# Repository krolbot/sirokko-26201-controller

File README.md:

# Sirokko 262.01

Контроллер для отопителя Sirokko 262.01: плата на ESP32-S3, прошивка и веб-пульт. Температура и режим работы задаются с панели с энкодером или с телефона по Wi-Fi.

[Прошивка](https://github.com/krolbot/sirokko-26201-controller/releases/latest/download/Sirokko-firmware.zip) · [Сборка и подключение](docs/assembly.md) · [Руководство пользователя](docs/user-guide.md) · [Компоненты и цены](hardware/BOM.md)

## Возможности

- Поддерживает температуру помещения или работает на заданном вручную уровне.
- Управляет розжигом и охлаждением, следит за температурой выхлопа и нагретого воздуха.
- Показывает графики температур, записывает измерения в CSV и отключает нагрев по таймеру.
- Обновляется по Wi-Fi.

## Устройство

Двухслойная плата **95 × 75 мм** питается от стабилизированного блока **12 или 24 В**. На ней устанавливаются **YD-ESP32-S3 N16R8 V1.4** и два модуля **MAX31856** для термопар K. Температуру помещения измеряет **DS18B20**.

Свеча и топливная муфта подключаются через внешние реле с катушками под напряжение выбранного БП. Двигателем управляет **HC-160A S2**. Силовая проводка отопителя проходит отдельно от платы контроллера.

Плата и прошивка пока не испытывались на собранном отопителе.

## Файлы проекта

| Каталог | Содержимое |
|---|---|
| [hardware](hardware/README.md) | Схема и плата Fusion Electronics, PDF, библиотека и ведомость компонентов |
| [firmware](firmware/README.md) | Исходники и сборка прошивки ESP32-S3 и веб-интерфейса Svelte |
| [manufacturing](manufacturing/README.md) | Gerber, параметры заказа платы, сборочный чертёж и монтажные координаты |
| [docs](docs/) | Сборка, подключение и использование |

[Выпуски](https://github.com/krolbot/sirokko-26201-controller/releases) · [Вопросы и ошибки](https://github.com/krolbot/sirokko-26201-controller/issues)

## Лицензии

Общая лицензия проекта не назначена. Лицензии сторонних материалов: [библиотеки KiCad](hardware/KICAD_LIBRARIES_LICENSE.md), [прошивка](firmware/README.md#сторонние-материалы), [веб-интерфейс](firmware/web_ui/THIRD_PARTY_NOTICES.txt).

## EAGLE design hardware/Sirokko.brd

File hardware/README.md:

# Плата контроллера

Двухслойная плата 95 × 75 мм с питанием от стабилизированного БП 12 или 24 В. ESP32 и модули термопар устанавливаются в колодки; силовые нагрузки подключаются через внешние реле и моторный контроллер.

## Модули

- YD-ESP32-S3 N16R8 V1.4 с внешней антенной, два ряда по 22 контакта.
- Два модуля MAX31856 с геометрией и распиновкой Adafruit 3263.
- Панель ST7789 2,4″ с энкодером EC11 и кнопкой KEY0, питание и логика 3,3 В.
- Моторный контроллер HC-160A S2 и две катушки реле под напряжение БП, до 0,25 А каждая.

## Питание и защита

F1 на 2 А и двунаправленный TVS SMBJ30CA защищают вход перед TPS26600. TPS26600 отключает питание при переполюсовке, перенапряжении, перегрузке и коротком замыкании. При перегрузке он повторяет попытки запуска; также предусмотрена тепловая защита.

| Параметр | Значение |
|---|---|
| Рабочее питание | Стабилизированный БП 12 или 24 В DC |
| Запуск после подачи питания | Около 10,2 В; расчётный диапазон 9,72–10,81 В |
| Отключение при снижении питания | Около 9,4 В; расчётный диапазон 8,93–9,93 В |
| Отключение по перенапряжению | Около 28 В; расчётный диапазон 26,59–29,77 В |
| Возврат после перенапряжения | Около 25,9 В; расчётный диапазон 24,65–27,34 В |
| Ограничение входного тока | Около 1 А |
| Плавный пуск | Около 10 мс при 12 В и 21 мс при 24 В |
| Выход K7805-1000R3 | 5 В / 1 А; бюджет электроники — 0,70 А |
| Питание датчиков и панели | 3,3 В от TLV1117LV33 |

Плата работает от 12 и 24 В без переключения. Катушки реле выбираются под напряжение БП: защита с порогом 28 В не защищает катушки 12 В от подключения к 24 В.

Пороги TPS26600 задают R101 (249 кОм), R103 (21 кОм) и R102 (12 кОм). Расчётные диапазоны учитывают допуск резисторов 1%, ТКС ±100 ppm/°C при −40…+85 °C, допуски порогов и входных токов из [даташита TI](https://www.ti.com/lit/ds/symlink/tps2660.pdf).

На входе K7805 установлен C101, 10 мкФ, 50 В, X7R — по типовой схеме [Mornsun](https://www.mornsun-power.com/public/uploads/pdf/K78xx-1000R3(L).pdf) для питания 12/24 В. Порог отключения TPS26600 с учётом допусков ниже 30 В.

Периферия питается от отдельного стабилизатора 3,3 В. Тепло от его площадки U102.4 отводится в сплошной полигон +3,3 В на верхнем слое. Ключи AO3422 управляют катушками реле; D20/D21 подавляют выбросы напряжения, RP20/RP21 удерживают ключи выключенными при старте ESP32. Внешние сигнальные линии защищены сборками SRV05-4.

## Файлы

| Файл | Назначение |
|---|---|
| [Sirokko.sch](Sirokko.sch), [Sirokko.brd](Sirokko.brd) | Связанные схема и плата Fusion Electronics в формате EAGLE |
| [Sirokko.lbr](Sirokko.lbr), [Sirokko-parts.lbr](Sirokko-parts.lbr) | Библиотеки компонентов и посадочных мест |
| [Sirokko.edru](Sirokko.edru) | Правила проектирования и проверки платы в Fusion |
| [schematic.pdf](schematic.pdf) | Схема в PDF |
| [BOM.md](BOM.md), [bom.csv](bom.csv) | Ведомость компонентов с артикулами и ценами |

Схему и плату открывают вместе в Fusion Electronics. Символы и посадочные места встроены в файлы. После импорта платы загрузите `Sirokko.edru` через **Design Rules → Load**: формат EAGLE не сохраняет все правила Fusion.

[Крепление и подключения](../docs/assembly.md) · [Изготовление платы](../manufacturing/README.md) · [Лицензии библиотек](KICAD_LIBRARIES_LICENSE.md)

## Верхний слой

## Нижний слой (вид сверху)

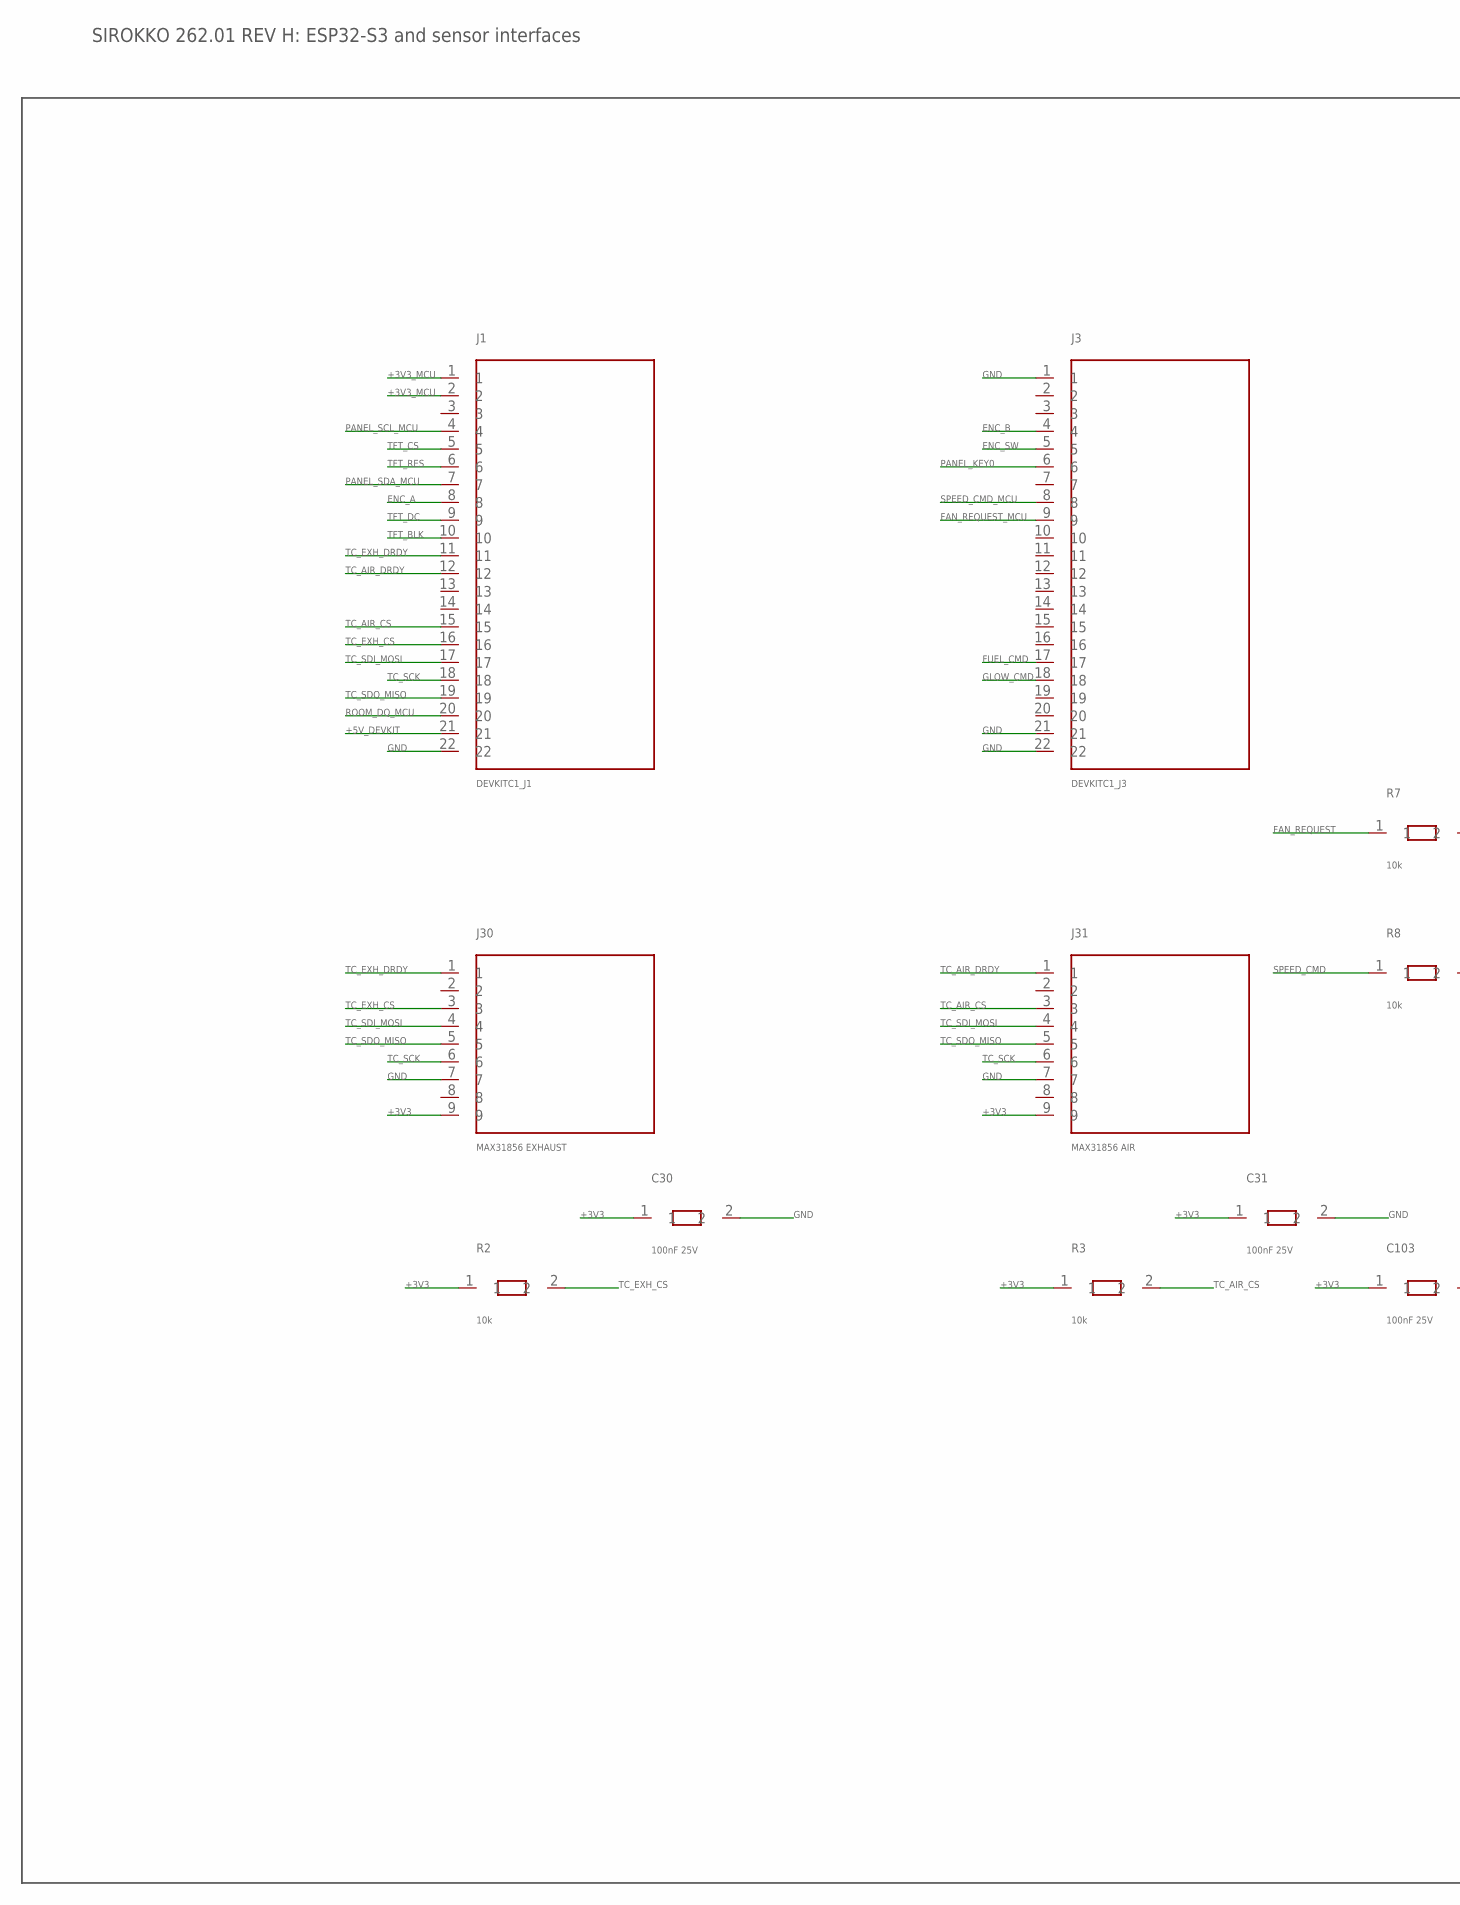
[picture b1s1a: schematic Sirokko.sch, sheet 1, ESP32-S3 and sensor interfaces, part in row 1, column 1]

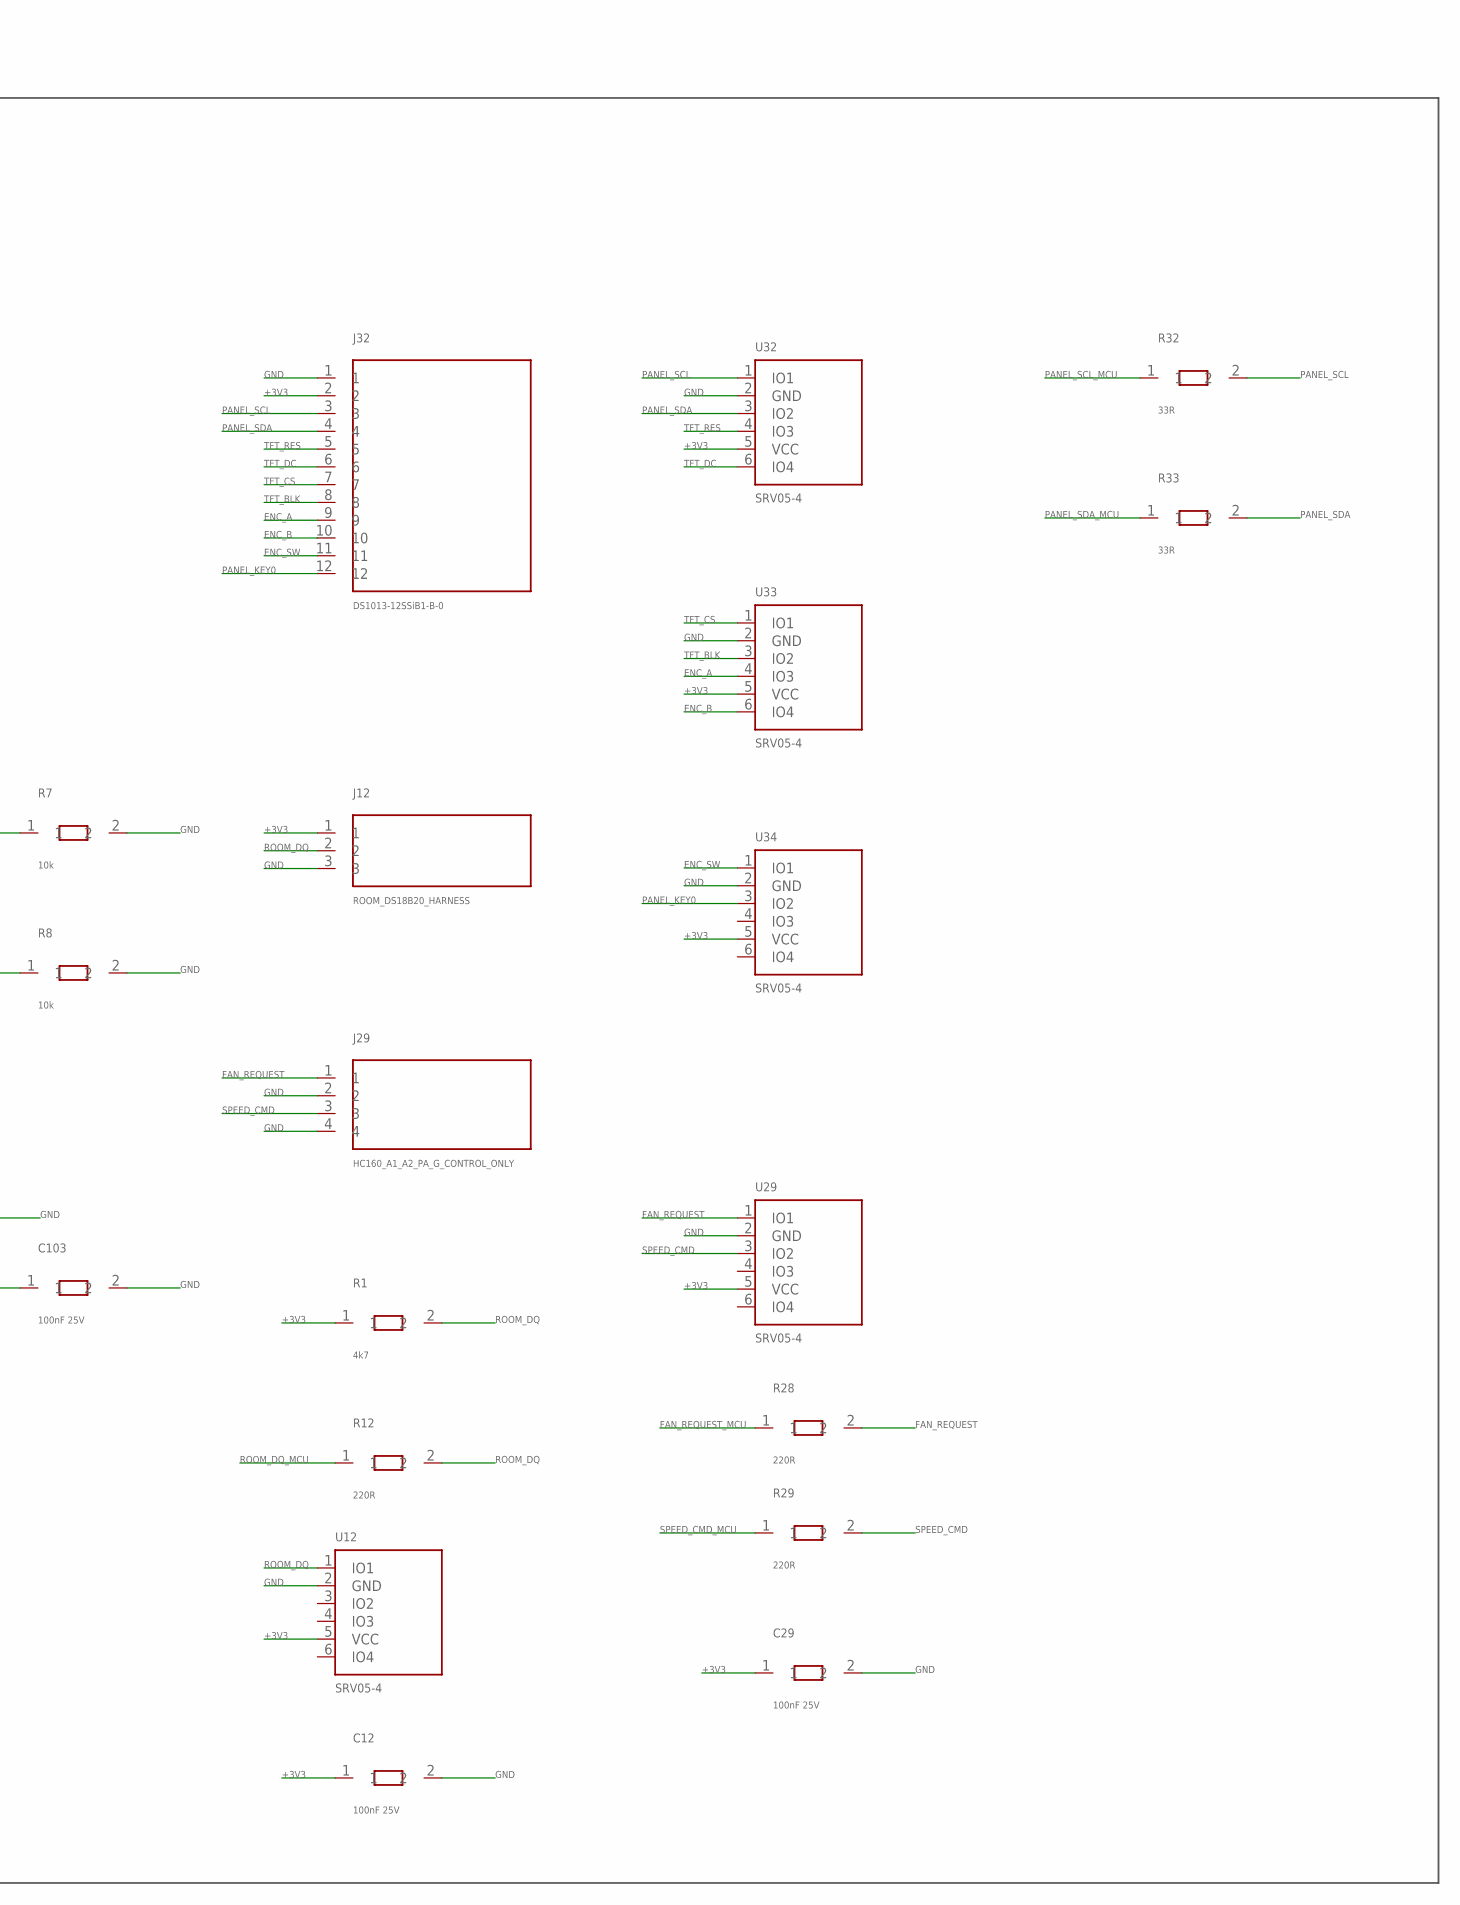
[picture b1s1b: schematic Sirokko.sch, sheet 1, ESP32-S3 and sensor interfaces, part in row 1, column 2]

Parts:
C12, C29, C30, C31, C103: 100nF 25V; C0805; MPN CC0805KRX7R8BB104
J1: DEVKITC1_J1; SOCKET_1X22_P2.54; MPN DS1023-1x40
J3: DEVKITC1_J3; SOCKET_1X22_P2.54; MPN DS1023-1x40
J12: ROOM_DS18B20_HARNESS; TERM_5.08_3; MPN DG127-5.08-03P-14-1000Z(H)
J29: HC160_A1_A2_PA_G_CONTROL_ONLY; TERM_5.08_4; MPN DG127-5.08-02P-14-00A(H)
J30: MAX31856 EXHAUST; SOCKET_MAX31856; MPN DS1023-1x40
J31: MAX31856 AIR; SOCKET_MAX31856; MPN DS1023-1x40
J32: DS1013-12SSiB1-B-0; DS1013_12SSIB1; MPN DS1013-12SSiB1-B-0
R1: 4k7; R0805; MPN RC0805FR-074K7L
R2, R3, R7, R8: 10k; R0805; MPN RC0805FR-0710KL
R12, R28, R29: 220R; R0805; MPN RC0805FR-07220RL
R32, R33: 33R; R0805; MPN RC0805FR-0733RL
U12, U29, U32, U33, U34: SRV05-4; SRV05_SOT23_6

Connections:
+3V3: C12.1, C29.1, C30.1, C31.1, C103.1, J12.1, J30.9, J31.9, J32.2, R1.1, R2.1, R3.1, U12.5 (VCC), U29.5 (VCC), U32.5 (VCC), U33.5 (VCC), U34.5 (VCC); also elsewhere on the board
+3V3_MCU: J1.1, J1.2
+5V_DEVKIT: J1.21; also elsewhere on the board
ENC_A: J1.8, J32.9, U33.4 (IO3)
ENC_B: J3.4, J32.10, U33.6 (IO4)
ENC_SW: J3.5, J32.11, U34.1 (IO1)
FAN_REQUEST: J29.1, R7.1, R28.2, U29.1 (IO1)
FAN_REQUEST_MCU: J3.9, R28.1
FUEL_CMD: J3.17; also elsewhere on the board
GLOW_CMD: J3.18; also elsewhere on the board
GND: C12.2, C29.2, C30.2, C31.2, C103.2, J1.22, J3.1, J3.21, J3.22, J12.3, J29.2, J29.4, J30.7, J31.7, J32.1, R7.2, R8.2, U12.2 (GND), U29.2 (GND), U32.2 (GND), U33.2 (GND), U34.2 (GND); also elsewhere on the board
PANEL_KEY0: J3.6, J32.12, U34.3 (IO2)
PANEL_SCL: J32.3, R32.2, U32.1 (IO1)
PANEL_SCL_MCU: J1.4, R32.1
PANEL_SDA: J32.4, R33.2, U32.3 (IO2)
PANEL_SDA_MCU: J1.7, R33.1
ROOM_DQ: J12.2, R1.2, R12.2, U12.1 (IO1)
ROOM_DQ_MCU: J1.20, R12.1
SPEED_CMD: J29.3, R8.1, R29.2, U29.3 (IO2)
SPEED_CMD_MCU: J3.8, R29.1
TC_AIR_CS: J1.15, J31.3, R3.2
TC_AIR_DRDY: J1.12, J31.1
TC_EXH_CS: J1.16, J30.3, R2.2
TC_EXH_DRDY: J1.11, J30.1
TC_SCK: J1.18, J30.6, J31.6
TC_SDI_MOSI: J1.17, J30.4, J31.4
TC_SDO_MISO: J1.19, J30.5, J31.5
TFT_BLK: J1.10, J32.8, U33.3 (IO2)
TFT_CS: J1.5, J32.7, U33.1 (IO1)
TFT_DC: J1.9, J32.6, U32.6 (IO4)
TFT_RES: J1.6, J32.5, U32.4 (IO3)

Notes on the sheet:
SIROKKO 262.01 REV H: ESP32-S3 and sensor interfaces

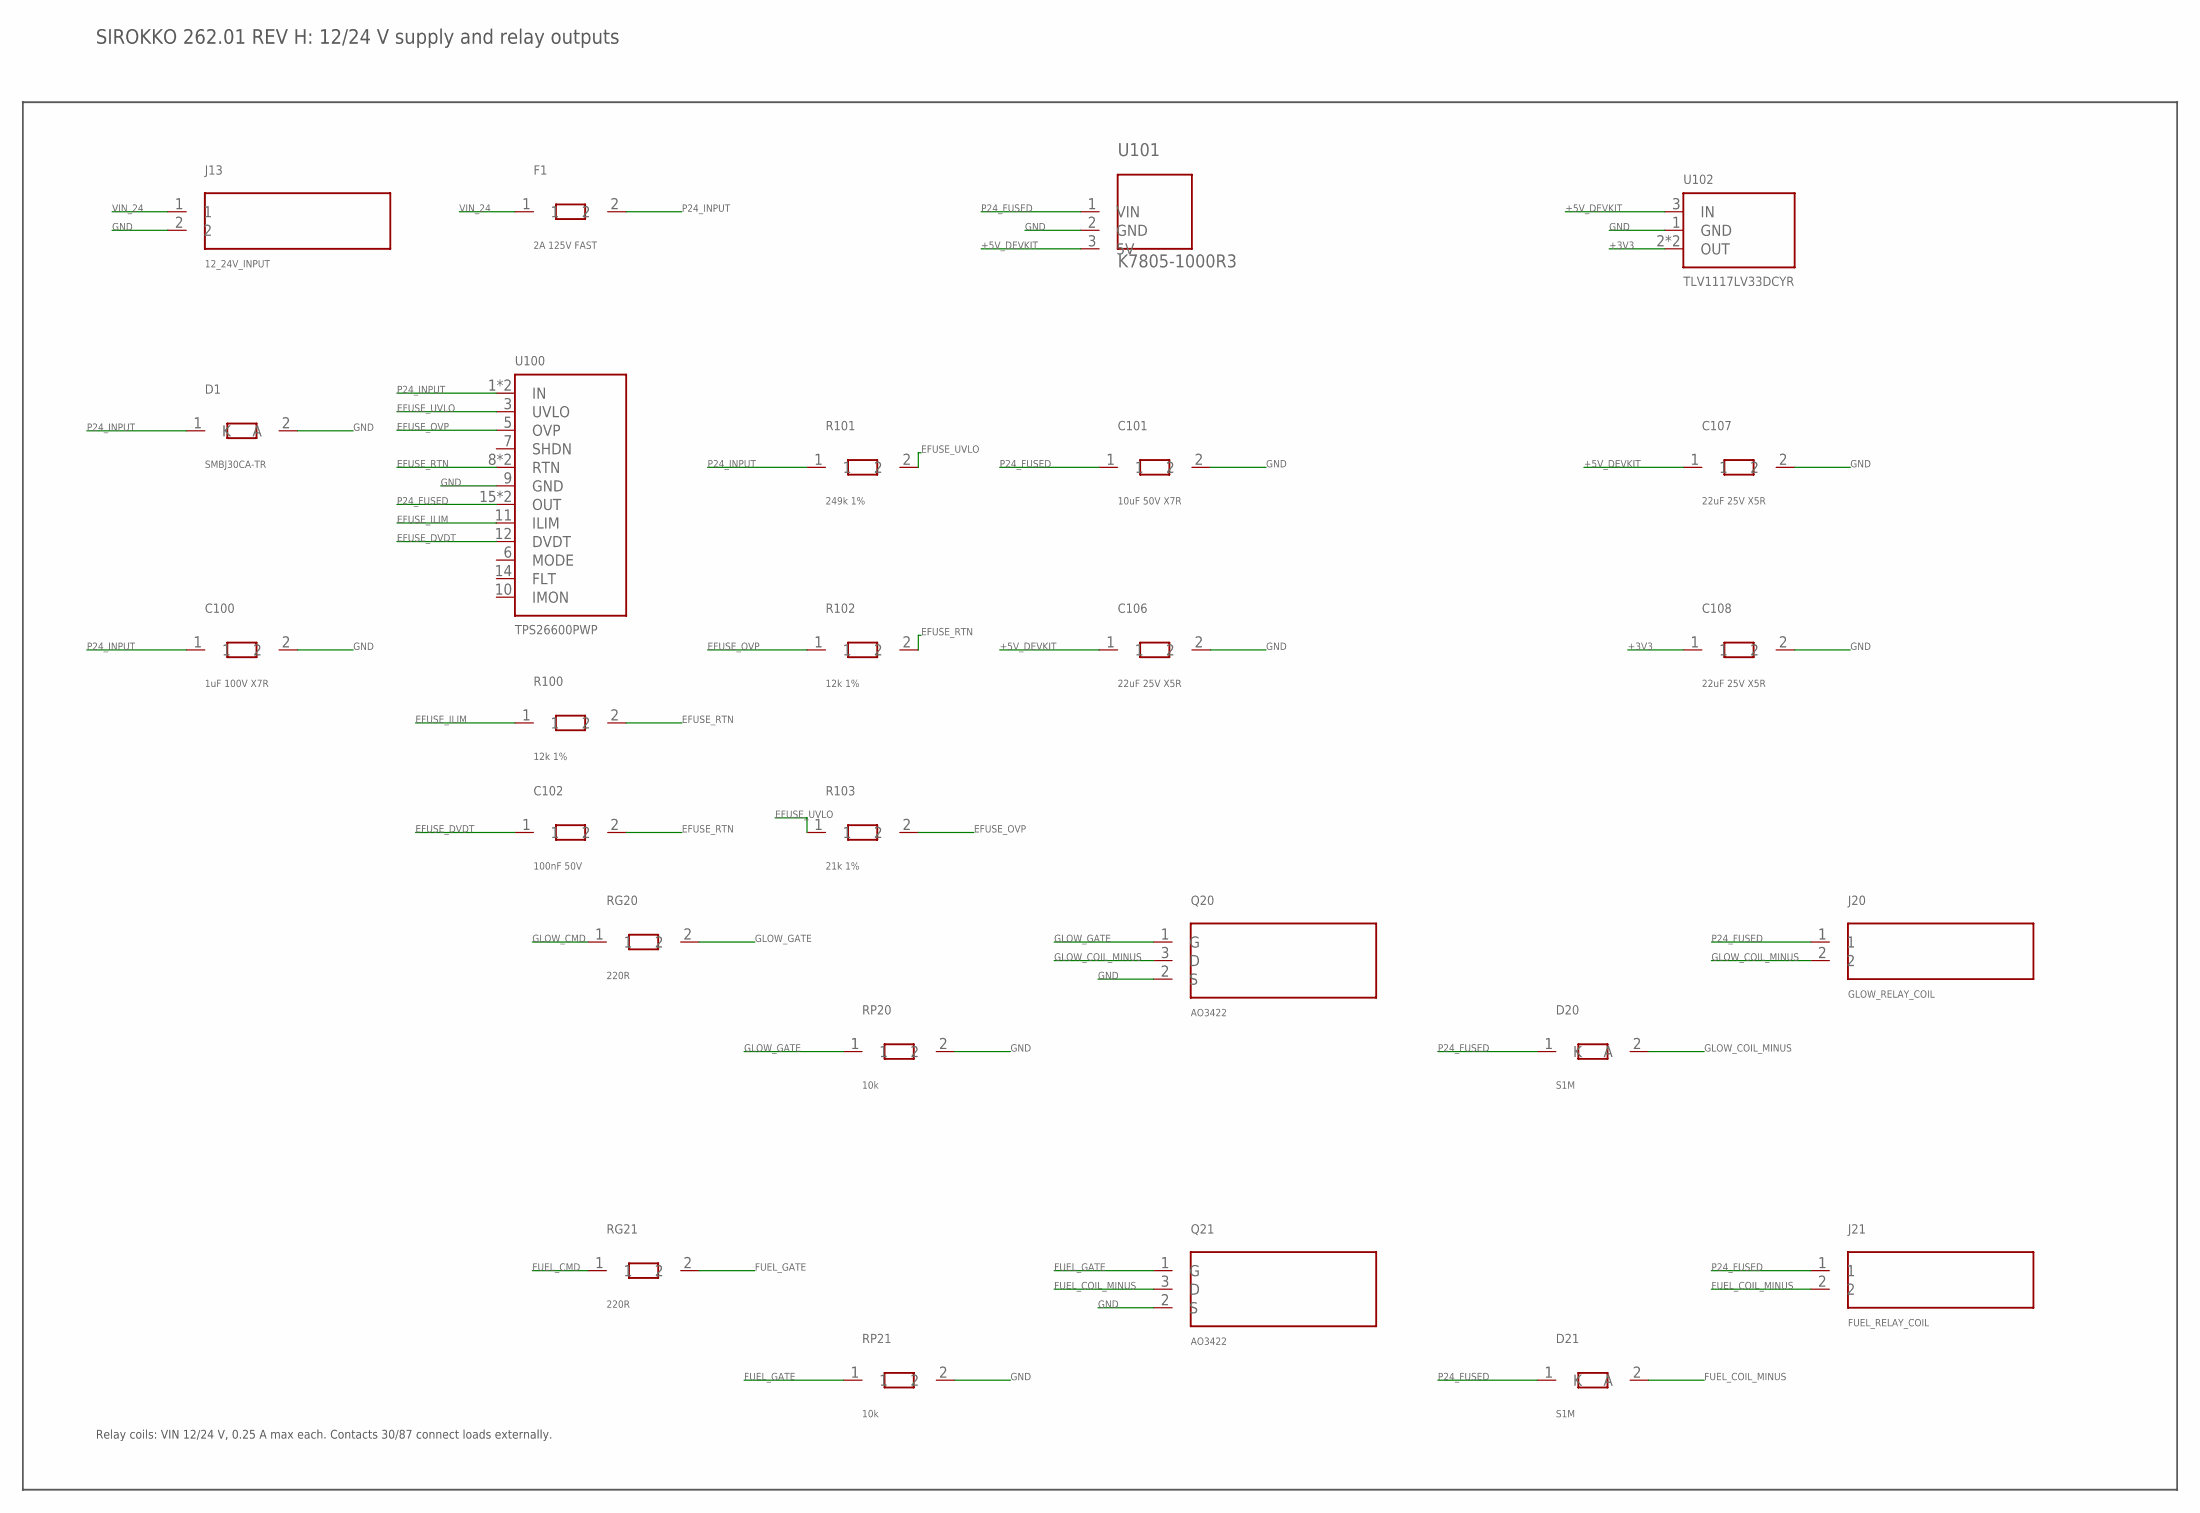
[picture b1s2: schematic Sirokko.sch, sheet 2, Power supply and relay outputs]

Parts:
C100: 1uF 100V X7R; C1206; MPN CC1206KKX7R0BB105
C101: 10uF 50V X7R; C1210; MPN GRM32ER71H106KA12L
C102: 100nF 50V; C1206; MPN CL31B104KBCNNNC
C106, C107, C108: 22uF 25V X5R; C1206; MPN CL31A226KAHNNNE
D1: SMBJ30CA-TR; SMB; MPN SMBJ30CA-TR
D20, D21: S1M; SMA; MPN S1M-13-F
F1: 2A 125V FAST; FUSE2410; MPN 0451002.MRL
J13: 12_24V_INPUT; TERM_5.08_2; MPN DG127-5.08-02P-14-00A(H)
J20: GLOW_RELAY_COIL; TERM_5.08_2; MPN DG127-5.08-02P-14-00A(H)
J21: FUEL_RELAY_COIL; TERM_5.08_2; MPN DG127-5.08-02P-14-00A(H)
Q20, Q21: AO3422; AO3422_SOT23
R100, R102: 12k 1%; R0805; MPN RC0805FR-0712KL
R101: 249k 1%; R0805; MPN RC0805FR-07249KL
R103: 21k 1%; R0805; MPN RC0805FR-0721KL
RG20, RG21: 220R; R0805; MPN RC0805FR-07220RL
RP20, RP21: 10k; R0805; MPN RC0805FR-0710KL
U100: TPS26600PWP; TPS26600_PWP
U101: K7805-1000R3; K7805_1000R3; MPN K7805-1000R3
U102: TLV1117LV33DCYR; TLV1117LV_DCY

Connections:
+3V3: C108.1, U102.2 (OUT), U102.4 (OUT); also elsewhere on the board
+5V_DEVKIT: C106.1, C107.1, U101.3 (5V), U102.3 (IN); also elsewhere on the board
EFUSE_DVDT: C102.1, U100.12 (DVDT)
EFUSE_ILIM: R100.1, U100.11 (ILIM)
EFUSE_OVP: R102.1, R103.2, U100.5 (OVP)
EFUSE_RTN: C102.2, R100.2, R102.2, U100.8 (RTN), U100.17 (RTN)
EFUSE_UVLO: R101.2, R103.1, U100.3 (UVLO)
FUEL_CMD: RG21.1; also elsewhere on the board
FUEL_COIL_MINUS: D21.2 (A), J21.2, Q21.3 (D)
FUEL_GATE: Q21.1 (G), RG21.2, RP21.1
GLOW_CMD: RG20.1; also elsewhere on the board
GLOW_COIL_MINUS: D20.2 (A), J20.2, Q20.3 (D)
GLOW_GATE: Q20.1 (G), RG20.2, RP20.1
GND: C100.2, C101.2, C106.2, C107.2, C108.2, D1.2 (A), J13.2, Q20.2 (S), Q21.2 (S), RP20.2, RP21.2, U100.9 (GND), U101.2 (GND), U102.1 (GND); also elsewhere on the board
P24_FUSED: C101.1, D20.1 (K), D21.1 (K), J20.1, J21.1, U100.15 (OUT), U100.16 (OUT), U101.1 (VIN)
P24_INPUT: C100.1, D1.1 (K), F1.2, R101.1, U100.1 (IN), U100.2 (IN)
VIN_24: F1.1, J13.1

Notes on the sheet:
SIROKKO 262.01 REV H: 12/24 V supply and relay outputs
Relay coils: VIN 12/24 V, 0.25 A max each. Contacts 30/87 connect loads externally.

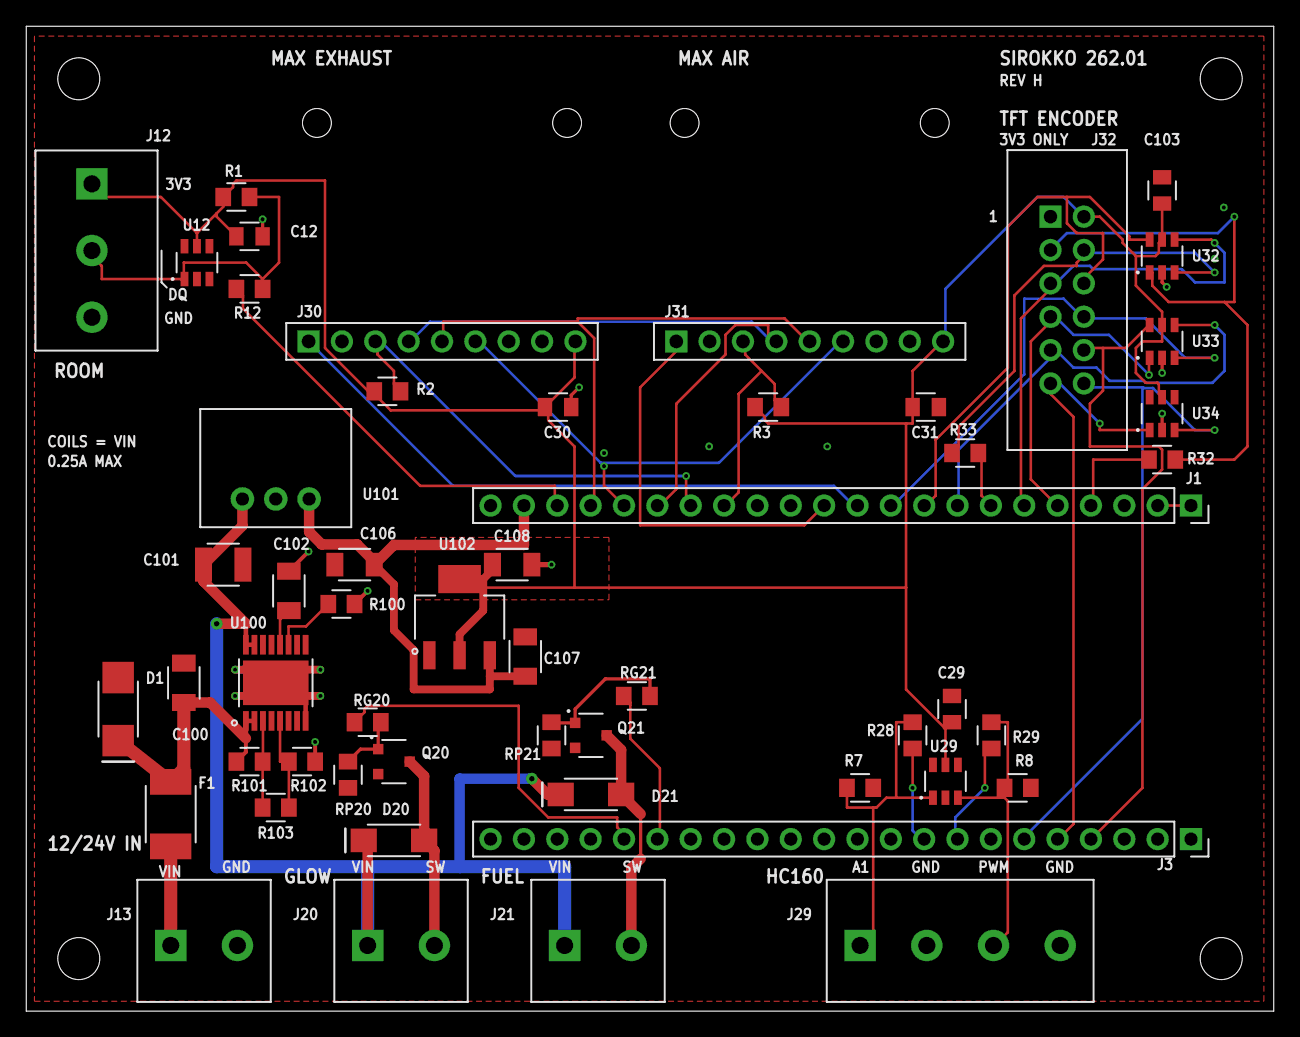
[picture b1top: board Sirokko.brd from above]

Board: 2 copper layers, 95.0 x 75.0 mm, 53 parts (0 on the bottom side), 43 nets.

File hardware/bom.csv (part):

Reference,Value,MPN,Package,Quantity,Mount,Side,Note,Supplier,SupplierURL,UnitPriceRUB,PriceUnit,PriceDate,MinimumOrder,OrderMultiple,PriceOffer
C12,100nF 25V,CC0805KRX7R8BB104,C0805,1,SMT,top,X7R; питание защиты сигналов,ЧипДип,https://www.chipdip.ru/product/0.1mkf-x7r-25v-10-0805-cc0805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,5,piece,2026-11-16,5,5,Основное предложение
C29,100nF 25V,CC0805KRX7R8BB104,C0805,1,SMT,top,X7R; питание защиты сигналов,ЧипДип,https://www.chipdip.ru/product/0.1mkf-x7r-25v-10-0805-cc0805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,5,piece,2026-11-16,5,5,Основное предложение
C30,100nF 25V,CC0805KRX7R8BB104,C0805,1,SMT,top,X7R; питание MAX31856,ЧипДип,https://www.chipdip.ru/product/0.1mkf-x7r-25v-10-0805-cc0805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,5,piece,2026-11-16,5,5,Основное предложение
C31,100nF 25V,CC0805KRX7R8BB104,C0805,1,SMT,top,X7R; питание MAX31856,ЧипДип,https://www.chipdip.ru/product/0.1mkf-x7r-25v-10-0805-cc0805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,5,piece,2026-11-16,5,5,Основное предложение
C100,1uF 100V X7R,CC1206KKX7R0BB105,C1206,1,SMT,top,X7R; вход U100,ЧипДип,https://www.chipdip.ru/product/1mkf-x7r-100v-10-1206-cc1206k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,9,piece,2026-11-16,5,5,Основное предложение
C101,10uF 50V X7R,GRM32ER71H106KA12L,C1210,1,SMT,top,X7R; вход U101 после электронной защиты,ЧипДип,https://www.chipdip.ru/product/10mkf-x7r-50v-10-1210-grm32er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,28,piece,2026-11-16,5,5,Основное предложение
C102,100nF 50V,CL31B104KBCNNNC,C1206,1,SMT,top,X7R; плавный пуск U100,ЧипДип,https://www.chipdip.ru/product/0.1mkf-x7r-50v-10-1206-cl31b1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,6,piece,2026-11-16,1,1,Основное предложение
C103,100nF 25V,CC0805KRX7R8BB104,C0805,1,SMT,top,X7R; питание защиты панели,ЧипДип,https://www.chipdip.ru/product/0.1mkf-x7r-25v-10-0805-cc0805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,5,piece,2026-11-16,5,5,Основное предложение
C106,22uF 25V X5R,CL31A226KAHNNNE,C1206,1,SMT,top,"X5R, 25 В",ЧипДип,https://www.chipdip.ru/product/22mkf-x5r-25v-10-1206-cl31a22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,12,piece,2026-11-16,1,1,Основное предложение
C107,22uF 25V X5R,CL31A226KAHNNNE,C1206,1,SMT,top,X5R; вход U102,ЧипДип,https://www.chipdip.ru/product/22mkf-x5r-25v-10-1206-cl31a22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,12,piece,2026-11-16,1,1,Основное предложение
C108,22uF 25V X5R,CL31A226KAHNNNE,C1206,1,SMT,top,X5R; выход U102,ЧипДип,https://www.chipdip.ru/product/22mkf-x5r-25v-10-1206-cl31a22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,12,piece,2026-11-16,1,1,Основное предложение
D1,SMBJ30CA-TR,SMBJ30CA-TR,SMB,1,SMT,top,Двунаправленный TVS; полярности нет,ЧипДип,https://www.chipdip.ru/product/smbj30ca-tr-diod-zaschitnyy-6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,19,piece,2026-11-16,1,1,Основное предложение
D20,S1M,S1M-13-F,SMA,1,SMT,top,Катод — к плюсу катушки,ЧипДип,https://www.chipdip.ru/product/s1m-13-f-diod-vypryamitelnyy-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,5,piece,2026-11-16,1,1,Основное предложение
D21,S1M,S1M-13-F,SMA,1,SMT,top,Катод — к плюсу катушки,ЧипДип,https://www.chipdip.ru/product/s1m-13-f-diod-vypryamitelnyy-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,5,piece,2026-11-16,1,1,Основное предложение
F1,2A 125V FAST,0451002.MRL,FUSE2410,1,SMT,top,,ЧипДип,https://www.chipdip.ru/product/0451002-mrl-2a-125v-2410-pred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,23,piece,2026-11-16,1,1,Основное предложение
J1,DEVKITC1_J1,DS1023-1x40,SOCKET_1X22_P2.54,1,THT,top,Отрезок 22 контакта; две планки по 40 контактов на J1/J3/J30/J31,ЧипДип,https://www.chipdip.ru/product/pbs-40-ds1023-1x40-gnezdo-na-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,28,40-pin strip,2026-11-16,1,1,Основное предложение
J3,DEVKITC1_J3,DS1023-1x40,SOCKET_1X22_P2.54,1,THT,top,Отрезок 22 контакта; две планки по 40 контактов на J1/J3/J30/J31,ЧипДип,https://www.chipdip.ru/product/pbs-40-ds1023-1x40-gnezdo-na-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,28,40-pin strip,2026-11-16,1,1,Основное предложение
J12,ROOM_DS18B20_HARNESS,DG127-5.08-03P-14-1000Z(H),TERM_5.08_3,1,THT,top,,ЧипДип,https://www.chipdip.ru/product/dg127-5.08-03p-14-1000z-h-kle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,45,piece,2026-11-16,1,1,Альтернативное предложение
J13,12_24V_INPUT,DG127-5.08-02P-14-00A(H),TERM_5.08_2,1,THT,top,1: VIN 12/24 В; 2: GND,ЧипДип,https://www.chipdip.ru/product/dg127-5.08-02p-14-00a-h-klemm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,28,piece,2026-11-16,10,10,Основное; альтернатива для 5 плат: 19 ₽ от 32 шт.
J20,GLOW_RELAY_COIL,DG127-5.08-02P-14-00A(H),TERM_5.08_2,1,THT,top,"Катушка реле до 0,25 А; 1: VIN 12/24 В; 2: коммутируемый минус",ЧипДип,https://www.chipdip.ru/product/dg127-5.08-02p-14-00a-h-klemm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,28,piece,2026-11-16,10,10,Основное; альтернатива для 5 плат: 19 ₽ от 32 шт.
J21,FUEL_RELAY_COIL,DG127-5.08-02P-14-00A(H),TERM_5.08_2,1,THT,top,"Катушка реле до 0,25 А; 1: VIN 12/24 В; 2: коммутируемый минус",ЧипДип,https://www.chipdip.ru/product/dg127-5.08-02p-14-00a-h-klemm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,28,piece,2026-11-16,10,10,Основное; альтернатива для 5 плат: 19 ₽ от 32 шт.
J29,HC160_A1_A2_PA_G_CONTROL_ONLY,DG127-5.08-02P-14-00A(H),TERM_5.08_4,1,THT,top,Два состыкованных двухконтактных блока,ЧипДип,https://www.chipdip.ru/product/dg127-5.08-02p-14-00a-h-klemm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,28,piece,2026-11-16,10,10,Основное; альтернатива для 5 плат: 19 ₽ от 32 шт.
J30,MAX31856 EXHAUST,DS1023-1x40,SOCKET_MAX31856,1,THT,top,Отрезок 9 контактов из остатка планки J1/J3,ЧипДип,https://www.chipdip.ru/product/pbs-40-ds1023-1x40-gnezdo-na-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,28,40-pin strip,2026-11-16,1,1,Основное предложение
J31,MAX31856 AIR,DS1023-1x40,SOCKET_MAX31856,1,THT,top,Отрезок 9 контактов из остатка планки J1/J3,ЧипДип,https://www.chipdip.ru/product/pbs-40-ds1023-1x40-gnezdo-na-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,28,40-pin strip,2026-11-16,1,1,Основное предложение
J32,DS1013-12SSiB1-B-0,DS1013-12SSiB1-B-0,DS1013_12SSIB1,1,THT,top,IDC 2×6 с ключом; ответная розетка DS1016-12MA2BB; распайка кабеля — в docs/assembly.md,ЧипДип,https://www.chipdip.ru/product/idc-12m-ds1013-12-vilka-2.54m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,11,piece,2026-11-16,1,1,Основное предложение
Q20,AO3422,AO3422,AO3422_SOT23,1,SMT,top,"55 В; Rds(on) ≤0,2 Ом при Vgs=2,5 В; 1: G, 2: S, 3: D",ЧипДип,https://www.chipdip.ru/product/ao3422-tranzistor-n-mosfet-55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,17,piece,2026-11-16,1,1,Основное предложение
Q21,AO3422,AO3422,AO3422_SOT23,1,SMT,top,"55 В; Rds(on) ≤0,2 Ом при Vgs=2,5 В; 1: G, 2: S, 3: D",ЧипДип,https://www.chipdip.ru/product/ao3422-tranzistor-n-mosfet-55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,17,piece,2026-11-16,1,1,Основное предложение
R1,4k7,RC0805FR-074K7L,R0805,1,SMT,top,1%,ЧипДип,https://www.chipdip.ru/product/0.125vt-0805-4.7-kom-1-rc0805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,4,piece,2026-11-16,10,5,Основное предложение
R2,10k,RC0805FR-0710KL,R0805,1,SMT,top,1%,ЧипДип,https://www.chipdip.ru/product/0.125vt-0805-10-kom-1-rc0805f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,6,piece,2026-11-16,10,5,Основное предложение
R3,10k,RC0805FR-0710KL,R0805,1,SMT,top,1%,ЧипДип,https://www.chipdip.ru/product/0.125vt-0805-10-kom-1-rc0805f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,6,piece,2026-11-16,10,5,Основное предложение
R7,10k,RC0805FR-0710KL,R0805,1,SMT,top,1%,ЧипДип,https://www.chipdip.ru/product/0.125vt-0805-10-kom-1-rc0805f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,6,piece,2026-11-16,10,5,Основное предложение
R8,10k,RC0805FR-0710KL,R0805,1,SMT,top,1%,ЧипДип,https://www.chipdip.ru/product/0.125vt-0805-10-kom-1-rc0805f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,6,piece,2026-11-16,10,5,Основное предложение
R12,220R,RC0805FR-07220RL,R0805,1,SMT,top,1%; последовательно с внешней сигнальной линией,ЧипДип,https://www.chipdip.ru/product/0.125vt-0805-220-om-1-rc0805f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,6,piece,2026-11-16,1,1,Основное предложение
R28,220R,RC0805FR-07220RL,R0805,1,SMT,top,1%; последовательно с внешней сигнальной линией,ЧипДип,https://www.chipdip.ru/product/0.125vt-0805-220-om-1-rc0805f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,6,piece,2026-11-16,1,1,Основное предложение
R29,220R,RC0805FR-07220RL,R0805,1,SMT,top,1%; последовательно с внешней сигнальной линией,ЧипДип,https://www.chipdip.ru/product/0.125vt-0805-220-om-1-rc0805f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,6,piece,2026-11-16,1,1,Основное предложение
R32,33R,RC0805FR-0733RL,R0805,1,SMT,top,1%; последовательное согласование SPI панели,ЧипДип,https://www.chipdip.ru/product/rc0805fr-0733rl-yageo-8001790284,4,piece,2026-11-16,1,1,Основное предложение
R33,33R,RC0805FR-0733RL,R0805,1,SMT,top,1%; последовательное согласование SPI панели,ЧипДип,https://www.chipdip.ru/product/rc0805fr-0733rl-yageo-8001790284,4,piece,2026-11-16,1,1,Основное предложение
R100,12k 1%,RC0805FR-0712KL,R0805,1,SMT,top,1%; предел тока U100 около 1 А,ЧипДип,https://www.chipdip.ru/product/0.125vt-0805-12-kom-1-rc0805f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,6,piece,2026-11-17,1,1,Основное предложение
R101,249k 1%,RC0805FR-07249KL,R0805,1,SMT,top,1%; верхнее плечо делителя UVLO/OVP,ЧипДип,https://www.chipdip.ru/product/rc0805fr-07249kl-rezistor-yag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,1,piece,2026-11-16,1,1,Основное предложение
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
